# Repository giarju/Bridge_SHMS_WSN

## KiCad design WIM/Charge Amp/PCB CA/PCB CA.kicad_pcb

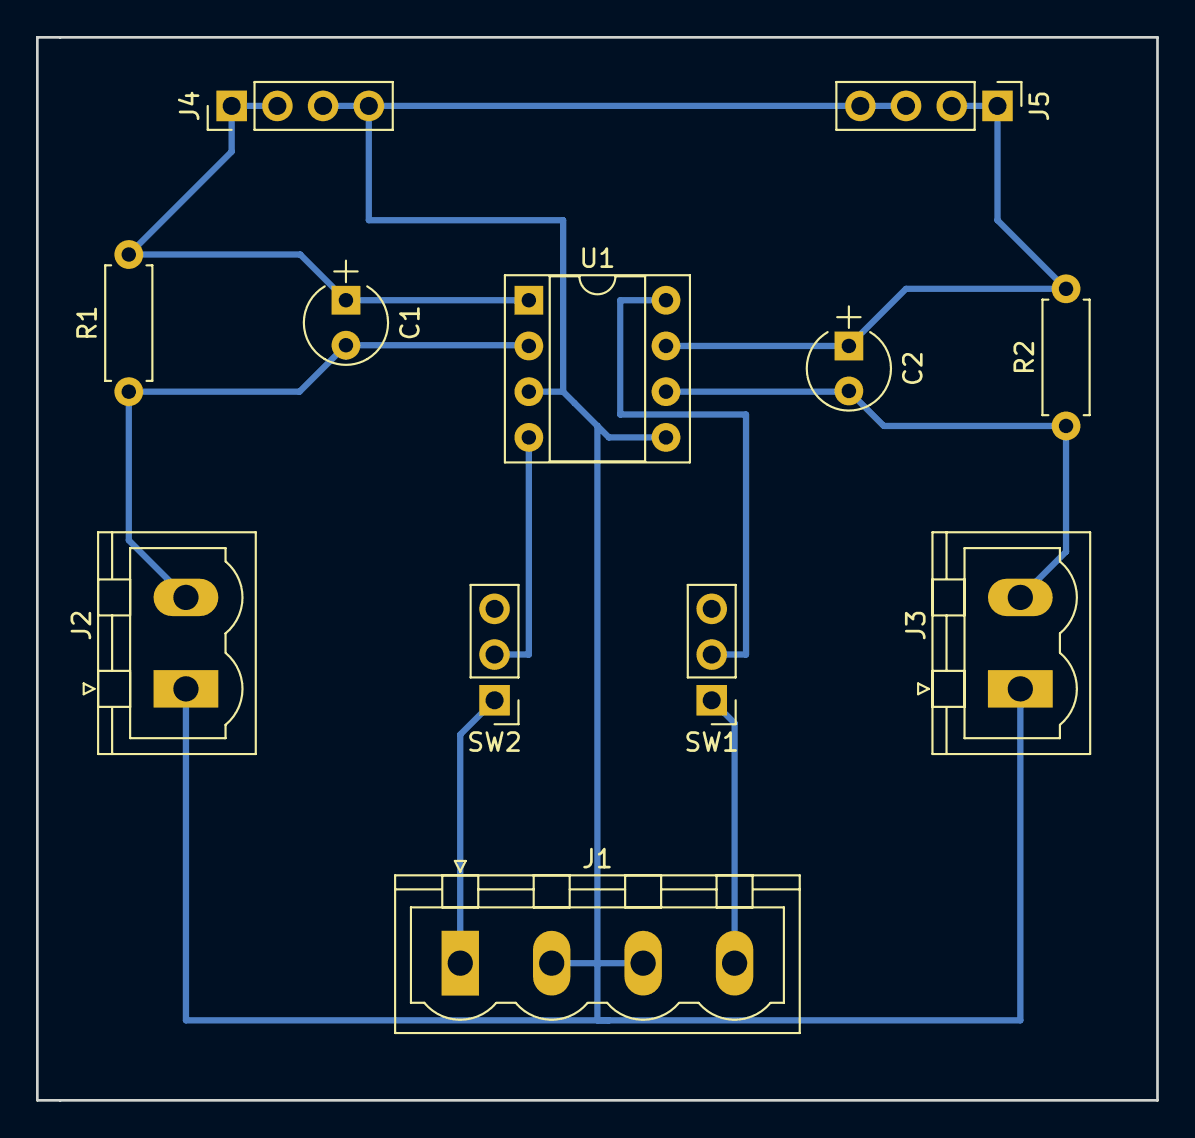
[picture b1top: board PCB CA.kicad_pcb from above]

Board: 2 copper layers, 62.2 x 59.1 mm, 12 parts (0 on the bottom side), 9 nets.

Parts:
C1, C2: 1n; CP_Radial_Tantal_D4.5mm_P2.50mm
J1: Power Port; PhoenixContact_MSTBVA-G_04x5.08mm_Vertical
J2: Vin1; PhoenixContact_MSTBVA-G_02x5.08mm_Vertical
J3: Vin2; PhoenixContact_MSTBVA-G_02x5.08mm_Vertical
J4: Vout1; Pin_Header_Straight_1x04_Pitch2.54mm
J5: Vout2; Pin_Header_Straight_1x04_Pitch2.54mm
R1, R2: 1M; R_Axial_DIN0207_L6.3mm_D2.5mm_P7.62mm_Horizontal
SW1, SW2: SW_DIP_x01; Pin_Header_Straight_1x03_Pitch2.54mm
U1: TL082; DIP-8_W7.62mm_Socket

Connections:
BAT+: J1.4, SW1.1
BAT-: J1.1, SW2.1
GND: J1.2, J1.3, J2.1, J3.1, J4.3, J4.4, J5.3, J5.4, U1.3, U1.5
unnamed: C1.1, J4.1, J4.2, R1.2, U1.1
unnamed: C1.2, J2.2, R1.1, U1.2
unnamed: C2.1, J5.1, J5.2, R2.2, U1.7
unnamed: C2.2, J3.2, R2.1, U1.6
unnamed: SW1.2, U1.8
unnamed: SW2.2, U1.4

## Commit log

2019-12-10 Rename Alif/p-wim.ino to Alif/WIM/p-wim_read.ino
2020-07-08 cleaniing files
2020-07-08 add recent files
2020-07-08 add schematic and PCB files
2020-07-08 recheck the files
2020-07-13 add sink folder
2020-07-13 add sink submodule
2020-07-14 add developer submodule and sink compile fix
2020-07-14 test submodule
2020-07-14 float ADC and GUI
2020-07-14 update ADC conversion
2020-07-16 add Wbee.java and Wim.java
2020-07-16 update to read Vpp from 2 channels
2020-07-18 sink add Storage class
2020-07-19 refactor Storage class
2020-07-20 create WIM class and implement it in ADC class
2020-07-20 ignore local settings
2020-07-20 initial commit utk kode wsn
2020-07-20 folder virtenio
2020-07-21 fix initialization method on Wim class
2020-07-21 fix count_axle method for two channels
2020-07-21 add init threshold method and display value in integer
2020-07-21 success Xbee connect to two PAN
2020-07-22 display time delay between two sensors
2020-07-22 add calculate_axle_weight method
2020-07-23 fix Xbee parsing and add rating function
2020-07-23 change static variable and method, create separate class for Print and Network
2020-07-23 change ADC oversample and fix axle_count method
2020-07-23 refactor sink project
2020-07-23 fix sink java warnig
2020-07-24 refactor sink storage package
2020-07-24 initial sink main class
2020-07-24 add activation method on Wim class
2020-07-24 add baseplate pdf files
2020-07-24 fix main and wim package
2020-07-24 change IP and fix comment
2020-07-26 change name in schematic
2020-07-27 change IP for plotter
2020-07-27 fix sink for integration test and add sink UML diagram
2020-07-28 change parse data
2020-07-30 add gui and update sink
2020-07-30 update graphic and fix Wim
2020-08-05 change IP
2020-08-05 fix bridge rating formula
2020-08-05 update sink and add penunjang300
2020-08-10 change server's credentials
2020-08-10 set UPBoard's IP as destination
2020-08-10 print axle and WSN Wake message
2020-09-13 add wavelet function
2020-09-18 implement interpolation to raw ADC data
2020-10-04 integrasi sistem
2020-10-04 update submodule
2021-04-02 Revert "Wsn"
2021-04-02 add virtenio folder
